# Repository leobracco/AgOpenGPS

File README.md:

# AgOpenGPS - Guidance software

Ag Precision Mapping and Section Control Software

AgOpenGPS is 2 programs. AgIO is the communication hub to the outside world and AgOpenGPS is the 
application. You can run either and within each, you can run the other.

You only need to run AgOpenGPS if you are using the simulator.

The software reads NMEA strings for the purpose of recording and mapping position information 
for Agricultural use. Also it has up to 16 sections of Section Control that can have unique widths 
or up to 64 same width sections to control implements application of product preventing 
over-application.

Also ouputs Pure pursuit steer angles from reference line for AB line, AB Curve and Contour guidance. 
Auto Headland called UTurn on Curve and AB Line with loops for narrow equipment. 
Mapping as a background can also be added.

## Shapefile overlay and MQTT publishing

The WinForms client can load ESRI Shapefiles and publish attributes of the
feature under the tractor via MQTT. At runtime use **Shapefile → Cargar
Shapefile...** to select a `.shp` file and toggle **Ver Shapefile** to enable
the overlay. Each position update queries the loaded dataset and publishes a
JSON payload to `agpvr/shape/current`:

```json
{
  "lat": -34.5678,
  "lon": -59.1234,
  "featureId": 123,
  "distance_m": 4.2,
  "attributes": { "ZONA": "A1", "KG_HA": 170 }
}
```

This feature uses [NetTopologySuite](https://github.com/NetTopologySuite) for
geometry handling and [MQTTnet](https://github.com/dotnet/MQTTnet) for MQTT
communication.

Included in this repository is an application, and source folders. 

See the PCB repo for PCB layouts, firmware for steering and rate control, machine control, GPS and simulator. 

## Installation

1. Download the [Most Stable AgOpenGPS Release](https://github.com/agopengps-official/AgOpenGPS/releases)
2. Unzip or extract the contents to a folder (folder accessible by user not the root of C:\\)
Even on your desktop
3. Run AgOpenGPS.exe

## Building

1. Clone this repository (e.g. use Visual Studio to do so)
2. Open the solution (`SourceCode/AgOpenGPS.sln`) in Visual Studio
3. Add your code and (re)build

## Contributing

The `master` branch contains the most stable version of AgOpenGPS, while the `develop` branch
is actively being worked on and may not be ready for production use.

In order to contribute to AgOpenGPS, follow these steps:

1. Checkout the `develop` branch
2. Create a new branch named after your feature
3. Make your changes and commit to this branch
4. Create a PR targeting the `develop` branch

## Links

- [AgOpenGPS Documentation](https://docs.agopengps.com/)
- [AgOpenGPS Forum](https://discourse.agopengps.com/)
- [PCB and Firmware Repository](https://github.com/agopengps-official/Boards)
- [SK21 Rate Control Repository](https://github.com/agopengps-official/Rate_Control)

## License

If you distribute copies of such a program, whether
gratis or for a fee, you must pass on to the recipients the same
freedoms that you received.  You must make sure that they, too, receive
or can get the source code.  And you must show them these terms so they
know their rights as Outlined in the GPLv3 License.

THIS SOFTWARE IS PROVIDED BY THE COPYRIGHT HOLDERS AND CONTRIBUTORS "AS IS" AND ANY EXPRESS OR IMPLIED WARRANTIES, INCLUDING, BUT NOT LIMITED TO, THE IMPLIED WARRANTIES OF MERCHANTABILITY AND FITNESS FOR A PARTICULAR PURPOSE ARE DISCLAIMED.
IN NO EVENT SHALL <COPYRIGHT HOLDER> BE LIABLE FOR ANY DIRECT, INDIRECT, INCIDENTAL, SPECIAL, EXEMPLARY, OR CONSEQUENTIAL DAMAGES (INCLUDING, BUT NOT LIMITED TO, PROCUREMENT OF SUBSTITUTE GOODS OR SERVICES;
LOSS OF USE, DATA, OR PROFITS; OR BUSINESS INTERRUPTION) HOWEVER CAUSED AND ON ANY THEORY OF LIABILITY, WHETHER IN CONTRACT, STRICT LIABILITY, OR TORT (INCLUDING NEGLIGENCE OR OTHERWISE) ARISING IN ANY WAY OUT OF THE USE OF THIS SOFTWARE, EVEN IF ADVISED OF THE POSSIBILITY OF SUCH DAMAGE.

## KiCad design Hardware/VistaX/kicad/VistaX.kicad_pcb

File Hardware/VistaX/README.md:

# VistaX node (hardware)

VistaX es un **nodo monitor de siembra** para AgOpenGPS, derivado del PCB
**RC15** del proyecto oficial de Rate Control
(`AgOpenGPS-Official/Rate_Control` → `ESP32/RC15`).

La idea: reutilizar la electrónica base de la RC15 (ESP32-WROOM-32U,
alimentación, Ethernet/USB, conector Ampseal de 23 pines, y el front-end de
sensor por **optoacoplador PC817** que ya trae para Flow1/Flow2) pero
**quitando la etapa de salida** (PCA9685 + 9× DRV8870) y reemplazándola por
**entradas aisladas por optoacoplador** para leer los sensores de semilla.

> Este repositorio es el **software de escritorio AgOpenGPS (C#/.NET)**.
> `Hardware/VistaX/` es una carpeta de hardware agregada; no afecta la
> compilación del software. El firmware del nodo es propio del usuario y
> queda fuera de alcance.

## Contenido

| Ruta | Qué es |
|---|---|
| `kicad/VistaX.kicad_pro/.kicad_prl` | Proyecto KiCad (RC15 renombrado a VistaX) |
| `kicad/VistaX.kicad_sch` | Hoja raíz (ESP32, PC817 Flow, jerarquía) |
| `kicad/DRVs.kicad_sch` | Etapa de salida RC15 **a reemplazar** (PCA9685 + DRV8870) |
| `kicad/Analog.kicad_sch` | Acondicionamiento analógico / ADS1115 (se conserva, opcional) |
| `kicad/Ethernet.kicad_sch` | Ethernet (W5500) — sin cambios |
| `kicad/VistaX.kicad_pcb` | PCB de la RC15 **renombrada** (ruteo intacto, ver límites) |
| `reference/` | PDFs de pinout/instalación/esquemático, foto y BOM **originales de la RC15** (sólo consulta) |
| `DESIGN.md` | Diseño del front-end de entradas por optoacoplador + guía de implementación en KiCad |
| `BOM-VistaX.md` | Listado de componentes consolidado (conservar / quitar / agregar) |

## Estado / alcance (importante, leer)

Hecho de forma confiable en este commit:

- Proyecto KiCad copiado y **rebrandeado** RC15 → VistaX: nombre de proyecto
  en todas las instancias de símbolo (212 ocurrencias), bloques de título
  del esquemático y del PCB, y serigrafía de la placa (`VistaX`).
- Documentación de ingeniería del rediseño (`DESIGN.md`): topología por
  canal, BOM delta, mapeo de conector y pines, y pasos en KiCad.
- Capa de protección/diagnóstico (`DESIGN.md` §6): fusible reseteable
  (eFuse con flag + PTC de respaldo, por grupo) y detección de
  abierto/corto por canal (bias + clasificación en firmware).
- PDFs/BOM originales de la RC15 conservados como referencia.

**NO** hecho (requiere KiCad y una persona — ver `DESIGN.md`):

- El `.kicad_pcb` (~1 MB, multicapa ya ruteado) **NO** fue modificado
  eléctricamente: sólo se rebrandeó. Quitar PCA9685/DRV8870, colocar la
  matriz de PC817 + expansor I2C y re-rutear/re-verter zonas debe hacerse
  en KiCad. Editar netlist/ruteo a mano corrompería la placa.
- El esquemático **no** fue re-cableado: se entrega el diseño y los pasos,
  no la modificación de netlist aplicada.
- Los gerbers/CPL **de VistaX** deben regenerarse desde el PCB ya
  modificado. En `reference/` se incluyen los gerbers **base de la RC15**
  (`GERBER-RC15-base.zip`) y renders, sólo como punto de partida/referencia.

Ver `DESIGN.md` para el diseño completo y la guía paso a paso.

## Importar en EasyEDA (leer si da error de formato)

El importador KiCad de **EasyEDA Pro** sólo acepta proyectos **KiCad ~5.x
(zipeados)**. Estos archivos son **KiCad 7** (`.kicad_sch` v20230121,
`.kicad_pcb` v20221018) → la importación directa falla con *"The imported
file format incorrect or doesn't match current type"*. Cambiar el número de
versión a mano **no** convierte la estructura (no funciona).

Caminos válidos:

1. **PCB en EasyEDA por Gerber** (sin KiCad): EasyEDA Pro →
   `Importar → Gerber` → `reference/GERBER-RC15-base.zip`. Da la placa base
   como lienzo/referencia (geometría de cobre/serigrafía, sin netlist).
2. **Rehacer el rediseño nativo en EasyEDA Pro** (lo más fiable): el
   circuito nuevo es chico (PC817 ×N + 2 expansores + eFuse/PTC + conexiones
   ESP32). EasyEDA Pro tiene integración LCSC/JLCPCB y `BOM-VistaX.md` ya
   trae los códigos LCSC. Usar `reference/RC15-Schematic.pdf` y los renders
   para los bloques que se conservan, y `DESIGN.md` para el front-end nuevo.
3. **Quedarse en KiCad**: `VistaX.kicad_pro` abre en KiCad 7+ y la guía
   (`DESIGN.md`) está escrita para KiCad. KiCad no exporta a 5.x, así que
   no hay puente directo a EasyEDA para el esquemático.

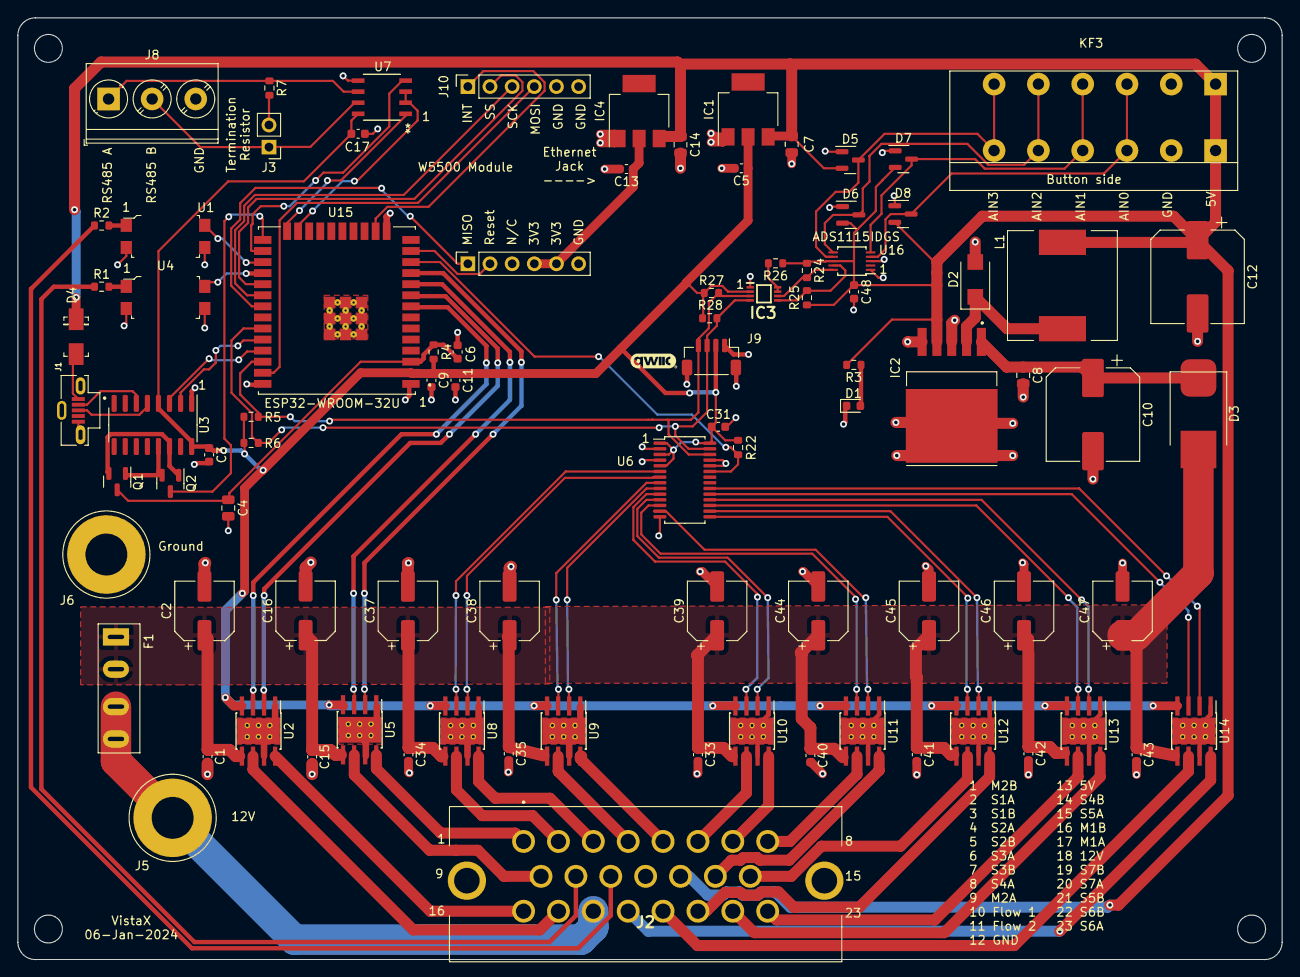
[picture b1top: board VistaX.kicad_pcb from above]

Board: 2 copper layers, 145.0 x 108.0 mm, 92 parts (0 on the bottom side), 82 nets.

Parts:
 : MountingHole_3.2mm_M3
 #2,  #3,  #4: MountingHole_3.2mm_M3
C1, C3, C6, C9, C15, C17, C31, C33, C34, C35, C40, C41, C42, C43, C48: 0.1uF; C_0603_1608Metric
C2, C16, C37, C38, C39, C44, C45, C46, C47: 47uF; CP_Elec_6.3x5.4
C4, C8: 1uF; C_0805_2012Metric
C5, C11, C13: 22uF; C_0603_1608Metric
C7, C14: 10uF; C_0805_2012Metric
C10: 470uF; CP_Elec_10x10.5
C12: 330uF; CP_Elec_10x10.5
D1: LED; LED_0603_1608Metric
D2: SS36; SMA(DO-214AC)
D3: S10MC; D_SMC_larger_pads
D4: M7 - C95872; DO-214AC
D5, D6, D7, D8: BAV99; SOT-23
F1: C492610; Fuse_Holder_C492610
IC1, IC4: AZ1117; SOT-223
IC2: XL2596; TO263-5L
IC3: PCA9306DCUR
J1: 105133-0011; MOLEX_105133-0011
J2: 776087-1-776087-1; 7760871
J3: Conn_01x02_Pin; PinHeader_1x02_P2.54mm_Vertical
J5: 12V; PowerPin
J6: Ground; PowerPin
J7, J10: Conn_01x06_Socket; PinSocket_1x06_P2.54mm_Vertical
J8: Screw_Terminal_01x03; TerminalBlock_Phoenix_PT-1,5-3-5.0-H_1x03_P5.00mm_Horizontal
J9: I2C; Qwic_vertical
KF3: KF142V-5.0-6P; KF142V-5.08-6P
L1: SMDRI127-330MT; TMPA1265SP-101MN-D
Q1, Q2: BSS138; SOT-23
R1, R2: 2.7K; R_0603_1608Metric
R3: 500; R_0603_1608Metric
R4, R22: 10K; R_0603_1608Metric
R5, R6: 2.2K; R_0603_1608Metric
R7: 120; R_0603_1608Metric
R24, R25: 341; R_0603_1608Metric
R26: 200K; R_0603_1608Metric
R27, R28: 217; R_0603_1608Metric
U1, U4: PC817 chip; SMD-4_4.6x7.62mm_P2.54mm
U2, U5, U8, U9, U10, U11, U12, U13, U14: DRV8870DDA; Texas_HTSOP-8-1EP_3.9x4.9mm_P1.27mm_EP2.95x4.9mm_Mask2.4x3.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
U3: CH340C; SOIC-16_3.9x9.9mm_P1.27mm
U6: PCA9685PW; TSSOP-28_4.4x9.7mm_P0.65mm
U7: C9943; 21-0041B_8_MXM
U15: ESP32-WROOM-32U; XCVR_ESP32-WROOM-32U
U16: ADS1115IDGS; TSSOP-10_3x3mm_P0.5mm

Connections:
+3.3V: C3.1, C5.1, C9.1, C11.1, C17.1, C31.1, IC1.2 (OUTPUT), IC3.2 (VREF1), J9.2, R4.1, R5.1, R6.1, R22.1, R27.1, R28.1, U2.4 (VREF), U3.4 (V3), U3.16 (VCC), U5.4 (VREF), U6.1 (A0), U6.3 (A2), U6.5 (A4), U6.28 (VDD), U7.8 (VCC), U8.4 (VREF), U9.4 (VREF), U10.4 (VREF), U11.4 (VREF), U12.4 (VREF), U13.4 (VREF), U14.4 (VREF), U15.2 (3V3)
+5V: C7.1, C12.1, C14.1, C48.1, D4.1 (K), D5.2 (A), D6.2 (A), D7.2 (A), D8.2 (A), IC1.3 (INPUT), IC2.4 (Feedback), IC4.3 (INPUT), J2.13, KF3.1, L1.2, R3.2, R24.1, R25.1, R26.1, U16.8 (VDD)
+12V: C1.1, C2.1, C15.1, C16.1, C33.1, C34.1, C35.1, C37.1, C38.1, C39.1, C40.1, C41.1, C42.1, C43.1, C44.1, C45.1, C46.1, C47.1, D3.2 (A), F1.1, U2.5 (VM), U5.5 (VM), U8.5 (VM), U9.5 (VM), U10.5 (VM), U11.5 (VM), U12.5 (VM), U13.5 (VM), U14.5 (VM)
FlowPin1: U4.4, U15.28 (IO17)
FlowPin2: U1.4, U15.27 (IO16)
FlowSensor1: J2.10, R1.1
FlowSensor2: J2.11, R2.1
GND: C1.2, C2.2, C3.2, C4.2, C5.2, C6.2, C7.2, C8.2, C9.2, C10.2, C11.2, C12.2, C13.2, C14.2, C15.2, C16.2, C17.2, C31.2, C33.2, C34.2, C35.2, C37.2, C38.2, C39.2, C40.2, C41.2, C42.2, C43.2, C44.2, C45.2, C46.2, C47.2, C48.2, D1.1 (K), D2.2, D5.1 (K), D6.1 (K), D7.1 (K), D8.1 (K), IC1.1 (ADJ/GND), IC2.3 (GND), IC2.5 (On/Off), IC2.6 (GND_1), IC3.1 (GND), IC4.1 (ADJ/GND), J1.5 (GND), J1.S1 (SHIELD), J1.S2 (SHIELD), J1.S3 (SHIELD), J2.12, J6.1, J7.6, J8.3, J9.1, J9.MP (MountPin), J10.5, J10.6, KF3.2, U1.2, U1.3, U2.1 (GND), U2.7 (ISEN), U2.9 (GND), U3.1 (GND), U4.2, U4.3, U5.1 (GND), U5.7 (ISEN), U5.9 (GND), U6.2 (A1), U6.4 (A3), U6.14 (VSS), U6.24 (A5), U6.25 (EXTCLK), U7.5 (GND), U8.1 (GND), U8.7 (ISEN), U8.9 (GND), U9.1 (GND), U9.7 (ISEN), U9.9 (GND), U10.1 (GND), U10.7 (ISEN), U10.9 (GND), U11.1 (GND), U11.7 (ISEN), U11.9 (GND), U12.1 (GND), U12.7 (ISEN), U12.9 (GND), U13.1 (GND), U13.7 (ISEN), U13.9 (GND), U14.1 (GND), U14.7 (ISEN), U14.9 (GND), U15.1 (GND), U15.15 (GND), U15.38 (GND), U15.G.1 (GND), U15.G.2 (GND), U15.G.4 (GND), U15.G.5 (GND), U15.G.6 (GND), U15.G.7 (GND), U15.G.8 (GND), U15.G.9 (GND), U15.G.10 (GND), U15.G.11 (GND), U15.G.12 (GND), U15.G.13 (GND), U15.G.14 (GND), U15.G.15 (GND), U15.G.16 (GND), U15.G.17 (GND), U15.G.18 (GND), U15.G.19 (GND), U15.G.20 (GND), U15.G.21 (GND), U15.G.22 (GND), U16.1 (ADDR), U16.3 (GND)
INTn: J10.1, U15.16 (IO13)
M1A: J2.17, U2.6 (OUT1)
M1B: J2.16, U2.8 (OUT2)
M1_IN1: U2.3 (IN1), U15.8 (I032)
M1_IN2: U2.2 (IN2), U15.9 (I033)
M2A: J2.9, U5.6 (OUT1)
M2B: J2.1, U5.8 (OUT2)
M2_IN1: U5.3 (IN1), U15.10 (I025)
M2_IN2: U5.2 (IN2), U15.11 (I026)
MISO: J7.1, U15.31 (IO19)
MOSI: J10.4, U15.37 (IO23)
unnamed: D1.2 (A), R3.1
unnamed: C8.1, C10.1, D3.1 (K), IC2.1 (VIN)
unnamed: D4.2 (A), J1.1 (VBUS)
unnamed: D2.1, IC2.2 (Output), L1.1
unnamed: IC3.7 (VREF2), IC3.8 (EN), R26.2
unnamed: IC3.6 (SCL2), R24.2, U16.10 (SCL)
unnamed: IC3.5 (SDA2), R25.2, U16.9 (SDA)
unnamed: C13.1, IC4.2 (OUTPUT), J7.4, J7.5
unnamed: J1.3 (D+), U3.5 (UD+)
unnamed: J1.2 (D-), U3.6 (UD-)
unnamed: J3.1, J8.2, U7.7 (B)
unnamed: J3.2, R7.2
unnamed: F1.2, J2.18, J5.1
unnamed: J8.1, R7.1, U7.6 (A)
unnamed: Q1.1 (G), Q2.2 (S), U3.13 (~DTR)
unnamed: Q1.2 (S), Q2.1 (G), U3.14 (~RTS)
unnamed: Q2.3 (D), U15.25 (IO0)
unnamed: R1.2, U4.1
unnamed: R2.2, U1.1
unnamed: U6.6 (LED0), U8.3 (IN1)
unnamed: U6.7 (LED1), U8.2 (IN2)
unnamed: U6.8 (LED2), U9.3 (IN1)
unnamed: U6.9 (LED3), U9.2 (IN2)
unnamed: U6.10 (LED4), U10.3 (IN1)
unnamed: U6.11 (LED5), U10.2 (IN2)
unnamed: U6.12 (LED6), U11.3 (IN1)
unnamed: U6.13 (LED7), U11.2 (IN2)
unnamed: U6.15 (LED8), U12.3 (IN1)
unnamed: U6.16 (LED9), U12.2 (IN2)
unnamed: U6.17 (LED10), U13.3 (IN1)
unnamed: U6.18 (LED11), U13.2 (IN2)
unnamed: U6.19 (LED12), U14.3 (IN1)
unnamed: U6.20 (LED13), U14.2 (IN2)
unnamed: D8.3 (K), KF3.3, U16.4 (AIN0)
unnamed: D7.3 (K), KF3.4, U16.5 (AIN1)
unnamed: D6.3 (K), KF3.5, U16.6 (AIN2)
unnamed: D5.3 (K), KF3.6, U16.7 (AIN3)
OutputEnable: R22.2, U6.23 (~OE), U15.12 (IO27)
RS485_Enable: U7.2 (~RE), U7.3 (DE), U15.23 (IO15)
RX2: U7.1 (RO), U15.24 (IO2)
ResetNW: J7.2, U15.13 (IO14)
S1A: J2.2, U8.6 (OUT1)
S1B: J2.3, U8.8 (OUT2)
S2A: J2.4, U9.6 (OUT1)
S2B: J2.5, U9.8 (OUT2)
S3A: J2.6, U10.6 (OUT1)
S3B: J2.7, U10.8 (OUT2)
S4A: J2.8, U11.6 (OUT1)
S4B: J2.14, U11.8 (OUT2)
S5A: J2.15, U12.6 (OUT1)
S5B: J2.21, U12.8 (OUT2)
S6A: J2.23, U13.6 (OUT1)
S6B: J2.22, U13.8 (OUT2)
S7A: J2.20, U14.6 (OUT1)
S7B: J2.19, U14.8 (OUT2)
SCK: J10.3, U15.30 (IO18)
SCL: IC3.3 (SCL1), J9.4, R5.2, R27.2, U6.26 (SCL), U15.36 (IO22)
SDA: IC3.4 (SDA1), J9.3, R6.2, R28.2, U6.27 (SDA), U15.33 (IO21)
SS: J10.2, U15.29 (IO5)
TX2: U7.4 (DI), U15.26 (IO4)
uC_EN: C4.1, C6.1, Q1.3 (D), R4.2, U15.3 (EN)
uC_RX: U3.2 (TXD), U15.34 (RXD0)
uC_TX: U3.3 (RXD), U15.35 (TXD0)

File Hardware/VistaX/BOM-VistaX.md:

# VistaX — Listado de componentes (BOM)

Consolidado del rediseño RC15 → monitor de siembra. Códigos **LCSC reales**
tomados de `reference/BOM-RC15.csv` donde la pieza se conserva o se reusa;
las piezas nuevas llevan especificación + candidato y `LCSC: a confirmar`
(no se inventan códigos).

Parámetro de escala: **N = canales de sensor**. Por defecto **N = 20**
(S1…S14 + M1A/M1B/M2A/M2B + Flow1/Flow2). De esos, 2 (Flow) ya están
equipados con PC817 (U1/U4); **canales nuevos a equipar = 18**.

---

## 1. CONSERVAR (de la RC15, sin cambios)

| Función | Ref | Valor / Parte | Footprint | LCSC |
|---|---|---|---|---|
| MCU | U15 | ESP32-WROOM-32U | XCVR_ESP32-WROOM-32U | C701344 |
| USB-UART | U3 | CH340C | SOIC-16 | C84681 |
| LDO 3V3 | IC1, IC4 | AZ1117 | SOT-223 | C92102 |
| Buck | IC2 | XL2596 | TO263-5L | C74190 |
| Inductor buck | L1 | SMDRI127-330MT | TMPA1265 | C9400 |
| Ethernet | U7 | (C9943) | 21-0041B_8_MXM | C9943 |
| Level-shift I2C | IC3 | PCA9306DCUR | PCA9306DCUR | C33196 |
| ADC (opcional) | U16 | ADS1115IDGS | TSSOP-10 | C37593 |
| Opto Flow (modelo a replicar) | U1, U4 | PC817 | SMD-4 | C66405 |
| Conector Ampseal | J2 | 776087-1 | 7760871 | C378893 |
| Conector | J1 | 105133-0011 | MOLEX_105133-0011 | C586226 |
| Bornera | KF3 | KF142V-5.0-6P | KF142V-5.08-6P | C475138 |
| Bornera tornillo | J8 | Screw_Terminal_01x03 | TerminalBlock PT-1,5-3 | C5188441 |
| Header 1x06 | J7, J10 | Conn_01x06_Socket | PinSocket 1x06 | C40877 |
| Qwiic I2C | J9 | I2C | Qwic_vertical | C160390 |
| Header 1x02 | J3 | Conn_01x02_Pin | PinHeader 1x02 | C7494857 |
| Power pin | J5, J6 | 12V / Ground | PowerPin | — |
| Portafusible entrada | F1 | C492610 | Fuse_Holder | C492610 |
| Diodo | D2 | SS36 | SMA | C2903825 |
| Diodo | D4 | M7 | DO-214AC | C95872 |
| Diodo | D3 | S10MC | D_SMC | C169472 |
| Clamp dual | D5–D8 | BAV99 | SOT-23 | C2500 |
| MOSFET nivel (Flow) | Q1, Q2 | BSS138 | SOT-23 | C255592 |
| LED estado | D1 | LED | LED_0603 | C84263 |
| R 200K | R26 | 200K | R_0603 | C105574 |
| R 2.7K | R1, R2 | 2.7K | R_0603 | C13167 |
| R 2.2K | R5, R6 | 2.2K | R_0603 | C4190 |
| R 500 | R3 | 500 | R_0603 | C22808 |
| R 341 | R24, R25 | 341 | R_0603 | C23138 |
| R 217 | R27, R28 | 217 | R_0603 | C25811 |
| R 120 | R7 | 120 | R_0603 | C22787 |
| R 10K | R4, R22 | 10K | R_0603 | C25804 |
| C 0.1uF | (15×) | 0.1uF | C_0603 | C14663 |
| C 1uF | C4, C8 | 1uF | C_0805 | C28323 |
| C 10uF | C7, C14 | 10uF | C_0805 | C15850 |
| C 22uF | C5, C11, C13 | 22uF | C_0603 | C59461 |
| C 47uF | (varias) | 47uF | CP_Elec | C2836440 |
| C 330uF | C12 | 330uF | CP_Elec 10x10.5 | C3032175 |
| C 470uF | C10 | 470uF | CP_Elec 10x10.5 | C310845 |

> Nota: del grupo 47uF (C2836440) y desacoplos asociados, **conservar sólo**
> los de la entrada/alimentación general; ver "QUITAR".

---

## 2. QUITAR (etapa de salida RC15)

| Función | Ref | Parte | LCSC | Cant. |
|---|---|---|---|---|
| Generador PWM I2C | U6 | PCA9685PW | C2678753 | 1 |
| Driver puente-H | U2, U5, U8, U9, U10, U11, U12, U13, U14 | DRV8870DDA | C86590 | 9 |
| Bulk/decoupling **exclusivos de los drivers** (subconjunto 47uF/0.1uF en rieles de driver) | varias | 47uF / 0.1uF | C2836440 / C14663 | criterio |

---

## 3. AGREGAR — front-end de entradas (sección 2–5 del DESIGN)

### 3.1 Por canal  (× N canales nuevos; por defecto ×18)

| Función | Valor / Parte | Footprint | LCSC | Cant. (N=18) |
|---|---|---|---|---|
| Optoacoplador entrada | PC817 (o array PC847 ×4) | SMD-4 | C66405 (igual que U1/U4) | 18 |
| R limitadora LED | ~1.2 kΩ, 0.25 W (1206 o 2×0603) | R_1206 | a confirmar (0603/1206) | 18 |
| Pull-up colector | 10 kΩ | R_0603 | C25804 (reuso) | 18 |
| Clamp/protección entrada | BAV99 | SOT-23 | C2500 (reuso) | 18 |
| C anti-rebote (opcional) | 1–10 nF | C_0603 | a confirmar | 18 |

### 3.2 Lectura I2C (fijo)

| Función | Parte candidata | LCSC | Cant. |
|---|---|---|---|
| Expansor de entrada I2C #1 | PCF8575 (o MCP23017) | a confirmar | 1 |
| Expansor de entrada I2C #2 (por presupuesto de bits, §6.3) | PCF8575 / MCP23017 (dir. distinta) | a confirmar | 1 |
| Decoupling expansores | 0.1uF | C14663 (reuso) | 2 |

---

## 4. AGREGAR — protección y diagnóstico (DESIGN §6)

| Función | Especificación / candidato | LCSC | Cant. |
|---|---|---|---|
| eFuse / smart high-side switch 12 V con FAULT | Vop ≥ 16 V, I-limit ajustable, salida diagnóstico, autorrecuperable. Cand.: TI TPS1HB08-Q1 / TPS2H160-Q1, Infineon Profet BTS500x | a confirmar | 1 (rama 12 V) |
| eFuse rama 5 V (si hay sensores 5 V) | TI TPS2553 / TPS25200 | a confirmar | 0–1 |
| PTC polyfuse respaldo | 1812, Vmax ≥ 30 V, I_hold ≥ Σ sensores, I_trip < límite eFuse | a confirmar | 1–2 |
| R bias por canal | 10 kΩ–22 kΩ | C25804 (10K, reuso) | × N (≈20) |
| Pull-up FAULT a +3V3 | 10 kΩ | C25804 (reuso) | 1 por flag (≈2) |

---

## 5. Resumen de cantidades (N = 20, 18 canales nuevos)

| Ítem | Cant. |
|---|---|
| PC817 nuevos | 18 (+2 existentes U1/U4) |
| R 1.2 kΩ (LED) | 18 |
| R 10 kΩ (pull-up colector) | 18 |
| R 10–22 kΩ (bias) | 20 |
| BAV99 (clamp entrada) | 18 (+ reuso D5–D8) |
| C 1–10 nF (debounce, opc.) | 18 |
| Expansor I2C | 2 |
| eFuse 12 V c/ FAULT | 1 |
| eFuse 5 V (opc.) | 0–1 |
| PTC 1812 | 1–2 |
| Pull-up FAULT 10 kΩ | ~2 |
| **QUITAR**: PCA9685 | 1 |
| **QUITAR**: DRV8870DDA | 9 |

---

## 6. Pendiente de selección antes de fabricar

Definir según los **sensores de siembra reales** (tensión y consumo):

1. `R_LED` exacta y potencia (recalcular con la tensión de sensor real).
2. Modelo de **eFuse** según corriente total de sensores y tensión (12/24 V).
3. **PTC** (I_hold/I_trip) coherente con el eFuse y con `F1`.
4. **Expansor** (PCF8575 vs MCP23017) y si parte de los canales van a
   **PCNT** nativo del ESP32 por alta tasa de pulso.
5. Códigos **LCSC** definitivos de las piezas nuevas (0603/1206, eFuse, PTC,
   expansor) al cerrar el esquemático en KiCad.

> Este listado es de diseño. La BOM/CPL fabricable se regenera desde el
> esquemático/PCB ya modificados en KiCad (ver `DESIGN.md` §5 y §6.5).
